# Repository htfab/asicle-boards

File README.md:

# Asicle boards

Contains two PCB designs for the Wordle clone on ASIC, [Asicle](https://github.com/htfab/asicle).

Asicle DIY uses only discrete transistors and passives for the supporting circuitry, with through-hole components for everything except the ASIC.

Asicle PRO uses standard commercial chips for voltage regulation, clock generation and VGA buffering for better reliability, and is designed with surface-mount components.

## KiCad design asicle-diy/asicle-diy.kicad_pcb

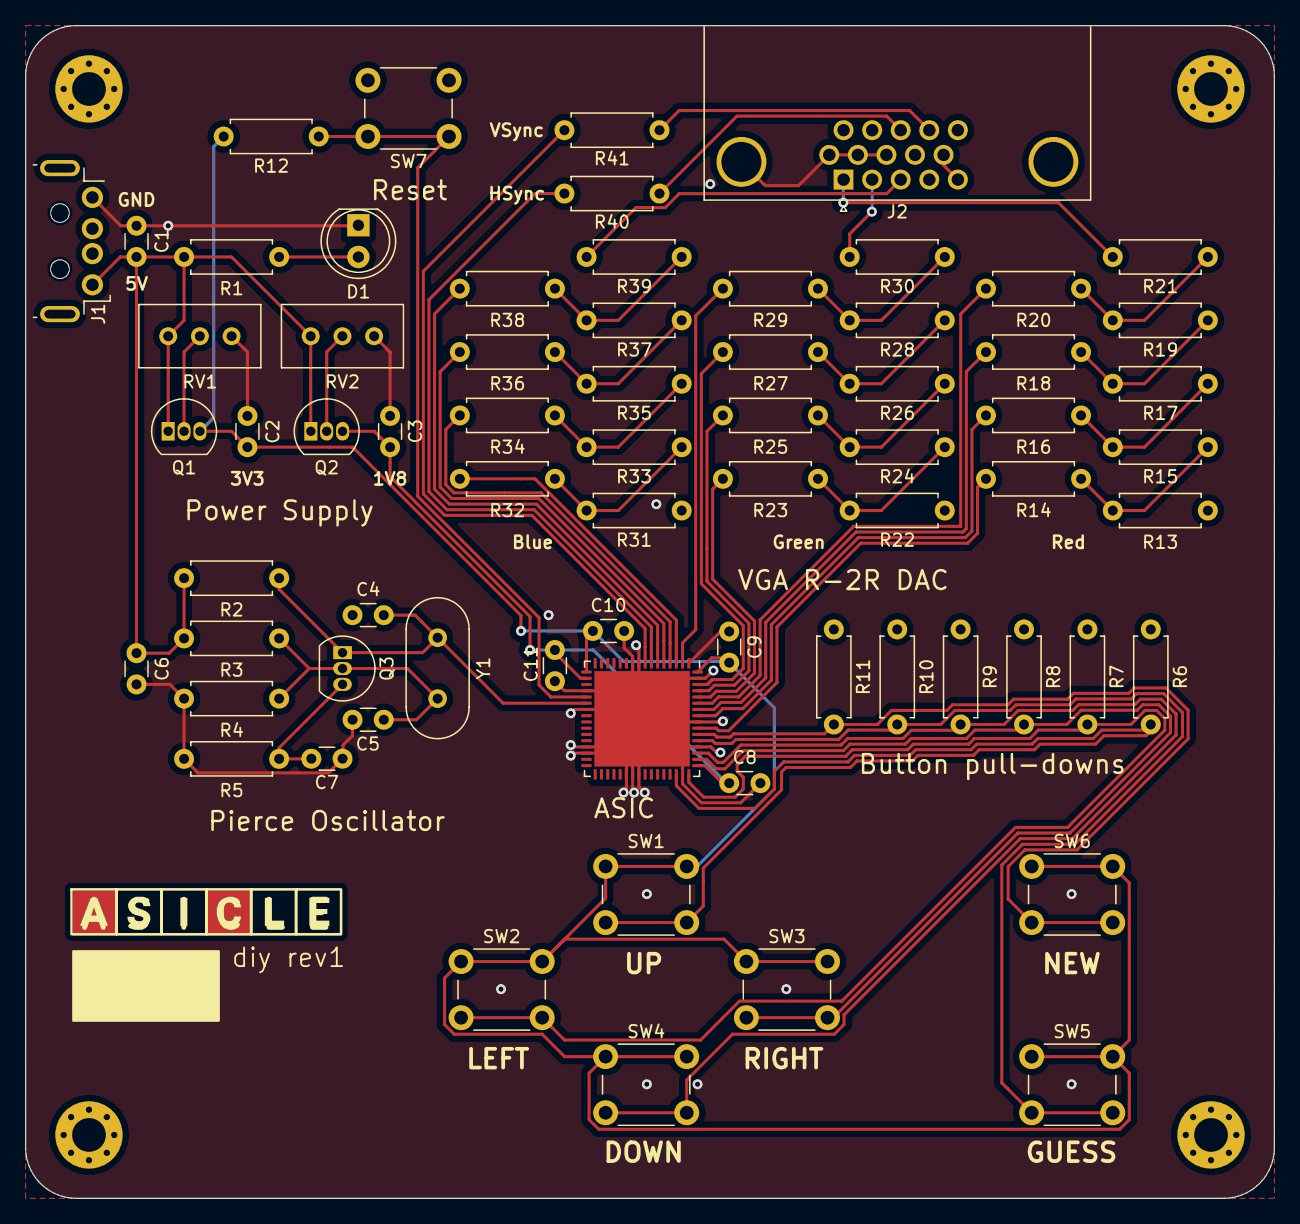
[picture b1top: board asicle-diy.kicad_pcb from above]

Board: 2 copper layers, 100.1 x 94.0 mm, 73 parts (0 on the bottom side), 48 nets.

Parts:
C1, C2, C3, C6, C7, C8, C9, C10, C11: 100n; C_Disc_D3.0mm_W1.6mm_P2.50mm
C4, C5: 22p; C_Disc_D3.0mm_W1.6mm_P2.50mm
D1: LED; LED_D5.0mm
H1, H2, H3, H4: MountingHole; MountingHole_2.7mm_M2.5_Pad_Via
J1: USB_A; USB_A_LC_THT
J2: DE15_Receptacle_HighDensity_MountingHoles; DSUB-15-HD_Female_Horizontal_P2.29x1.98mm_EdgePinOffset8.35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
Q1, Q2, Q3: BC548; TO-92_Inline
R1: 200; R_Axial_DIN0207_L6.3mm_D2.5mm_P7.62mm_Horizontal
R2: 3.3k; R_Axial_DIN0207_L6.3mm_D2.5mm_P7.62mm_Horizontal
R3, R6, R7, R8, R9, R10, R11, R12: 47k; R_Axial_DIN0207_L6.3mm_D2.5mm_P7.62mm_Horizontal
R4: 20k; R_Axial_DIN0207_L6.3mm_D2.5mm_P7.62mm_Horizontal
R5: 1k; R_Axial_DIN0207_L6.3mm_D2.5mm_P7.62mm_Horizontal
R13, R14, R16, R18, R20, R22, R23, R25, R27, R29, R31, R32, R34, R36, R38: 680; R_Axial_DIN0207_L6.3mm_D2.5mm_P7.62mm_Horizontal
R15, R17, R19, R24, R26, R28, R33, R35, R37: 270; R_Axial_DIN0207_L6.3mm_D2.5mm_P7.62mm_Horizontal
R21, R30, R39, R40, R41: 100; R_Axial_DIN0207_L6.3mm_D2.5mm_P7.62mm_Horizontal
RV1, RV2: 5k; Potentiometer_Bourns_3296W_Vertical
SW1: Up; SW_PUSH_6mm
SW2: Left; SW_PUSH_6mm
SW3: Right; SW_PUSH_6mm
SW4: Down; SW_PUSH_6mm
SW5: Guess; SW_PUSH_6mm
SW6: New; SW_PUSH_6mm
SW7: Reset; SW_PUSH_6mm
U3: Caravel; QFN-64-1EP_9x9mm_P0.5mm_EP7.65x7.65mm
Y1: 25MHz; Crystal_HC49-U_Vertical

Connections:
+1V8: C3.1, C8.1, C11.1, Q2.3 (E), U3.18 (vccd), U3.49 (vccd1)
+3V3: C2.1, C9.2, C10.1, Q1.3 (E), R12.2, SW1.1, SW2.1, SW3.1, SW4.1, SW5.1, SW6.1, U3.17 (vddio), U3.64 (vddio)
+5V: C1.1, C6.1, J1.1 (VBUS), Q1.1 (C), Q2.1 (C), R1.1, R2.1, R3.1, RV1.1, RV2.1
CLK: C4.2, Q3.1 (C), R2.2, U3.22 (clock), Y1.2
GND: C1.2, C2.2, C3.2, C4.1, C5.1, C6.2, C7.1, C8.2, C9.1, C10.2, C11.2, D1.1 (K), H1.1, H2.1, H3.1, H4.1, J1.4 (GND), J1.5 (Shield), J2.0, J2.5, J2.6, J2.7, J2.8, J2.10, R4.1, R5.1, R6.1, R7.1, R8.1, R9.1, R10.1, R11.1, R13.2, R22.1, R31.1, RV1.3, RV2.3, SW7.2, U3.1 (vssa2), U3.9 (vdda2), U3.10 (vssd2), U3.20 (vssa), U3.23 (vssd), U3.29 (vssio), U3.30 (vdda), U3.38 (vssa1), U3.39 (vssd1), U3.40 (vdda1), U3.47 (vdda1), U3.52 (vssa1), U3.56 (vssio), U3.63 (vccd2), U3.65 (ThermalPad)
IN_DOWN: R9.2, SW4.2, U3.51 (mprj_io[15])
IN_GUESS: R10.2, SW5.2, U3.53 (mprj_io[16])
IN_LEFT: R7.2, SW2.2, U3.48 (mprj_io[13])
IN_NEW: R11.2, SW6.2, U3.54 (mprj_io[17])
IN_RIGHT: R8.2, SW3.2, U3.50 (mprj_io[14])
IN_UP: R6.2, SW1.2, U3.46 (mprj_io[12])
unnamed: D1.2 (A), R1.2
unnamed: Q1.2 (B), RV1.2
unnamed: Q2.2 (B), RV2.2
unnamed: C5.2, Q3.2 (B), R3.2, R4.2, Y1.1
unnamed: C7.2, Q3.3 (E), R5.2
unnamed: R13.1, R14.2, R15.1
unnamed: R15.2, R16.2, R17.1
unnamed: R17.2, R18.2, R19.1
unnamed: R19.2, R20.2, R21.1
unnamed: R22.2, R23.2, R24.1
unnamed: R24.2, R25.2, R26.1
unnamed: R26.2, R27.2, R28.1
unnamed: R28.2, R29.2, R30.1
unnamed: R31.2, R32.2, R33.1
unnamed: R33.2, R34.2, R35.1
unnamed: R35.2, R36.2, R37.1
unnamed: R37.2, R38.2, R39.1
OUT_B0: R32.1, U3.3 (mprj_io[26])
OUT_B1: R34.1, U3.4 (mprj_io[27])
OUT_B2: R36.1, U3.5 (mprj_io[28])
OUT_B3: R38.1, U3.6 (mprj_io[29])
OUT_G0: R23.1, U3.60 (mprj_io[22])
OUT_G1: R25.1, U3.61 (mprj_io[23])
OUT_G2: R27.1, U3.62 (mprj_io[24])
OUT_G3: R29.1, U3.2 (mprj_io[25])
OUT_HS: R40.1, U3.7 (mprj_io[30])
OUT_R0: R14.1, U3.55 (mprj_io[18])
OUT_R1: R16.1, U3.57 (mprj_io[19])
OUT_R2: R18.1, U3.58 (mprj_io[20])
OUT_R3: R20.1, U3.59 (mprj_io[21])
OUT_VS: R41.1, U3.8 (mprj_io[31])
VGA_BLUE: J2.3, R39.2
VGA_GREEN: J2.2, R30.2
VGA_HSYNC: J2.13, R40.2
VGA_RED: J2.1, R21.2
VGA_VSYNC: J2.14, R41.2
~RST: R12.1, SW7.1, U3.21 (resetb)

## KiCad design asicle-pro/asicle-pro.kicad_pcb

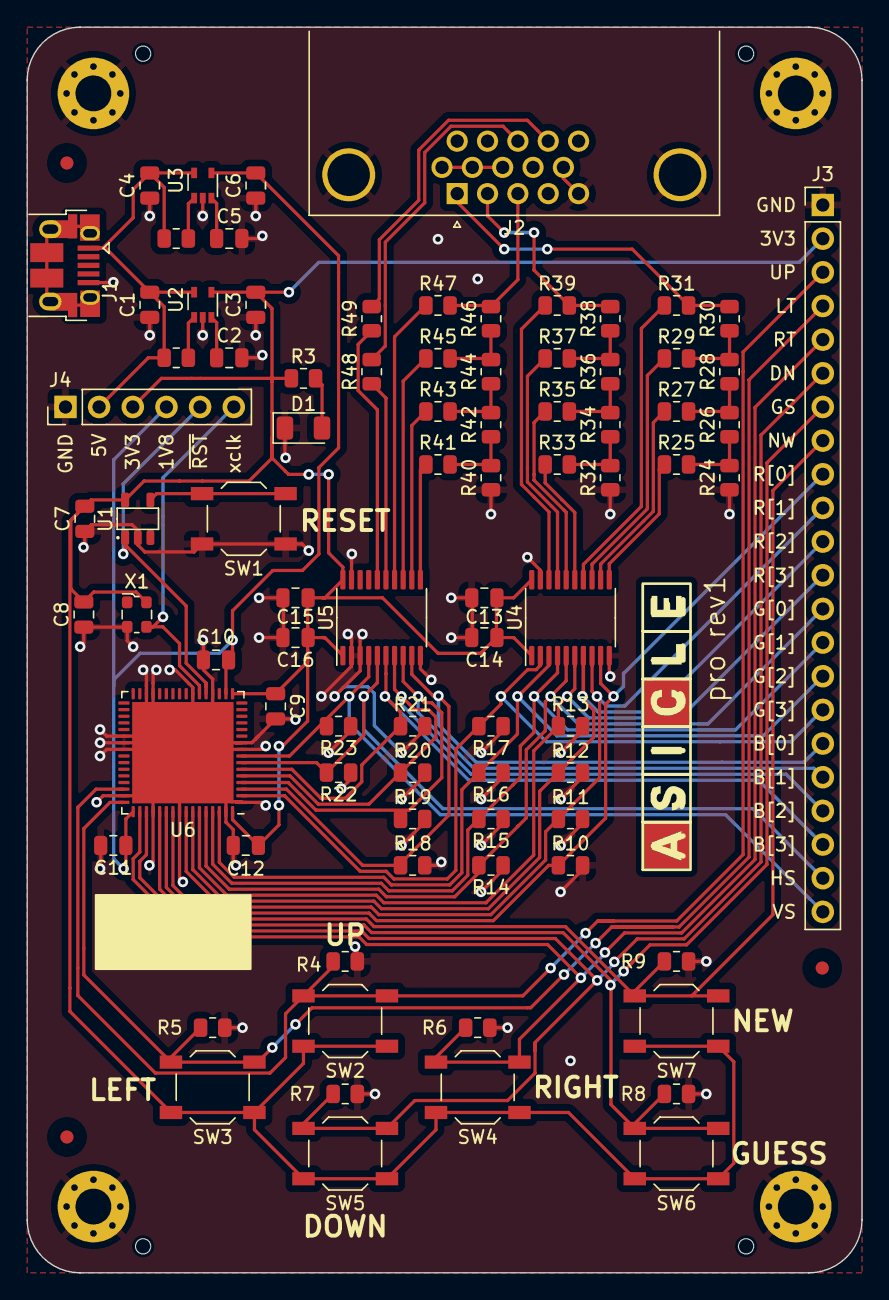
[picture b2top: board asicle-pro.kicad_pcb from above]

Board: 2 copper layers, 63.0 x 94.0 mm, 95 parts (0 on the bottom side), 60 nets.

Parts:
C1, C4, C13, C15: 1u; C_0805_2012Metric
C2, C5: 10n; C_0805_2012Metric
C3, C6: 10u; C_0805_2012Metric
C7, C8, C9, C10, C11, C12, C14, C16: 100n; C_0805_2012Metric
D1: LED - 17-215SURC/S530-A2/TR8; LED_1206_3216Metric
FID1, FID2, FID3: Fiducial; Fiducial_1mm_Mask3mm
H1, H2, H3, H4: MountingHole; MountingHole_2.7mm_M2.5_Pad_Via
H5, H6, H7, H8: ToolingHole; ToolingHole-JLCSMT
J1: USB_B_Micro - 10118193-0001LF; USB_Micro-B_Amphenol_10103594-0001LF_Horizontal
J2: DE15_Receptacle_HighDensity_MountingHoles; DSUB-15-HD_Female_Horizontal_P2.29x1.98mm_EdgePinOffset8.35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
J3: Conn_01x22_Pin; PinHeader_1x22_P2.54mm_Vertical
J4: Conn_01x06_Pin; PinHeader_1x06_P2.54mm_Vertical
R1, R2: 10k; R_0805_2012Metric
R3: 82; R_0805_2012Metric
R4, R5, R6, R7, R8, R9: 47k; R_0805_2012Metric
R10, R11, R12, R13, R14, R15, R16, R17, R18, R19, R20, R21, R22, R23: 100k; R_0805_2012Metric
R24, R25, R27, R29, R31, R32, R33, R35, R37, R39, R40, R41, R43, R45, R47: 536; R_0805_2012Metric
R26, R28, R30, R34, R36, R38, R42, R44, R46: 270; R_0805_2012Metric
R48, R49: 100; R_0805_2012Metric
SW1, SW2, SW3, SW4, SW5, SW6, SW7: SW_Push; SW_SPST_TL3342
U1: MCP1319MT-29LE-OT; PoR_5_SOT23
U2, U3: TAR5SxxU_SOT353F; SOT-353F
U4, U5: SN74ALVC245PWR; TSSOP-20_4.4x6.5mm_P0.65mm
U6: Caravel; QFN-64-1EP_9x9mm_P0.5mm_EP7.65x7.65mm
X1: 25MHz; Oscillator_SMD_ECS_2520MV-xxx-xx-4Pin_2.5x2.0mm

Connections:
+1V8: C6.2, C10.1, C11.1, J4.4, U3.4 (VOUT), U6.18 (vccd), U6.49 (vccd1)
+3V3: C3.2, C7.2, C8.2, C9.1, C12.2, C13.1, C14.1, C15.1, C16.1, J3.2, J4.3, R3.1, SW2.2, SW3.2, SW4.2, SW5.2, SW6.2, SW7.2, U1.5 (VDD), U2.4 (VOUT), U4.1 (DIR), U4.20 (VCC), U5.1 (DIR), U5.20 (VCC), U6.17 (vddio), U6.64 (vddio), X1.4 (V+)
+5V: C1.2, C4.2, J1.1 (VBUS), J4.2, R1.2, R2.2, U2.5 (VIN), U3.5 (VIN)
GND: C1.1, C2.2, C3.1, C4.1, C5.2, C6.1, C7.1, C8.1, C9.2, C10.2, C11.2, C12.1, C13.2, C14.2, C15.2, C16.2, D1.1 (K), H1.1, H2.1, H3.1, H4.1, J1.5 (GND), J2.0, J2.5, J2.6, J2.7, J2.8, J2.10, J3.1, J4.1, R4.2, R5.2, R6.2, R7.2, R8.2, R9.2, R10.2, R11.2, R12.2, R13.2, R14.1, R15.1, R16.1, R17.1, R18.2, R19.2, R20.2, R21.2, R22.1, R23.1, R24.1, R32.1, R40.1, SW1.1, U1.2 (VSS), U2.2 (GND), U3.2 (GND), U4.10 (GND), U4.19 (~OE), U5.2 (A1), U5.3 (A2), U5.10 (GND), U5.19 (~OE), U6.1 (vssa2), U6.9 (vdda2), U6.10 (vssd2), U6.20 (vssa), U6.23 (vssd), U6.29 (vssio), U6.30 (vdda), U6.38 (vssa1), U6.39 (vssd1), U6.40 (vdda1), U6.47 (vdda1), U6.52 (vssa1), U6.56 (vssio), U6.63 (vccd2), U6.65 (ThermalPad), X1.2 (GND)
IN_DOWN: J3.6, R7.1, SW5.1, U6.51 (mprj_io[15])
IN_GUESS: J3.7, R8.1, SW6.1, U6.53 (mprj_io[16])
IN_LEFT: J3.4, R5.1, SW3.1, U6.48 (mprj_io[13])
IN_NEW: J3.8, R9.1, SW7.1, U6.54 (mprj_io[17])
IN_RIGHT: J3.5, R6.1, SW4.1, U6.50 (mprj_io[14])
IN_UP: J3.3, R4.1, SW2.1, U6.46 (mprj_io[12])
unnamed: D1.2 (A), R3.2
unnamed: R24.2, R25.2, R26.1
unnamed: R26.2, R27.2, R28.1
unnamed: R28.2, R29.2, R30.1
unnamed: R32.2, R33.2, R34.1
unnamed: R34.2, R35.2, R36.1
unnamed: R36.2, R37.2, R38.1
unnamed: R40.2, R41.2, R42.1
unnamed: R42.2, R43.2, R44.1
unnamed: R44.2, R45.2, R46.1
unnamed: SW1.2, U1.4 (~MR)
unnamed: R1.1, U2.1 (Control)
unnamed: C2.1, U2.3 (Noise)
unnamed: R2.1, U3.1 (Control)
unnamed: C5.1, U3.3 (Noise)
OUT_B0: J3.17, R18.1, U5.9 (A8), U6.3 (mprj_io[26])
OUT_B1: J3.18, R19.1, U5.8 (A7), U6.4 (mprj_io[27])
OUT_B2: J3.19, R20.1, U5.7 (A6), U6.5 (mprj_io[28])
OUT_B3: J3.20, R21.1, U5.6 (A5), U6.6 (mprj_io[29])
OUT_G0: J3.13, R14.2, U4.5 (A4), U6.60 (mprj_io[22])
OUT_G1: J3.14, R15.2, U4.4 (A3), U6.61 (mprj_io[23])
OUT_G2: J3.15, R16.2, U4.3 (A2), U6.62 (mprj_io[24])
OUT_G3: J3.16, R17.2, U4.2 (A1), U6.2 (mprj_io[25])
OUT_HS: J3.21, R22.2, U5.5 (A4), U6.7 (mprj_io[30])
OUT_R0: J3.9, R10.1, U4.9 (A8), U6.55 (mprj_io[18])
OUT_R1: J3.10, R11.1, U4.8 (A7), U6.57 (mprj_io[19])
OUT_R2: J3.11, R12.1, U4.7 (A6), U6.58 (mprj_io[20])
OUT_R3: J3.12, R13.1, U4.6 (A5), U6.59 (mprj_io[21])
OUT_VS: J3.22, R23.2, U5.4 (A3), U6.8 (mprj_io[31])
VGA_B0: R41.1, U5.11 (B8)
VGA_B1: R43.1, U5.12 (B7)
VGA_B2: R45.1, U5.13 (B6)
VGA_B3: R47.1, U5.14 (B5)
VGA_BLUE: J2.3, R46.2, R47.2
VGA_G0: R33.1, U4.15 (B4)
VGA_G1: R35.1, U4.16 (B3)
VGA_G2: R37.1, U4.17 (B2)
VGA_G3: R39.1, U4.18 (B1)
VGA_GREEN: J2.2, R38.2, R39.2
VGA_HS: R48.1, U5.15 (B4)
VGA_HSYNC: J2.13, R48.2
VGA_R0: R25.1, U4.11 (B8)
VGA_R1: R27.1, U4.12 (B7)
VGA_R2: R29.1, U4.13 (B6)
VGA_R3: R31.1, U4.14 (B5)
VGA_RED: J2.1, R30.2, R31.2
VGA_VS: R49.1, U5.16 (B3)
VGA_VSYNC: J2.14, R49.2
xclk: J4.6, U6.22 (clock), X1.3 (OUT)
~RST: J4.5, U1.1 (~RST), U6.21 (resetb)

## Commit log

2024-04-10 add project to version control
